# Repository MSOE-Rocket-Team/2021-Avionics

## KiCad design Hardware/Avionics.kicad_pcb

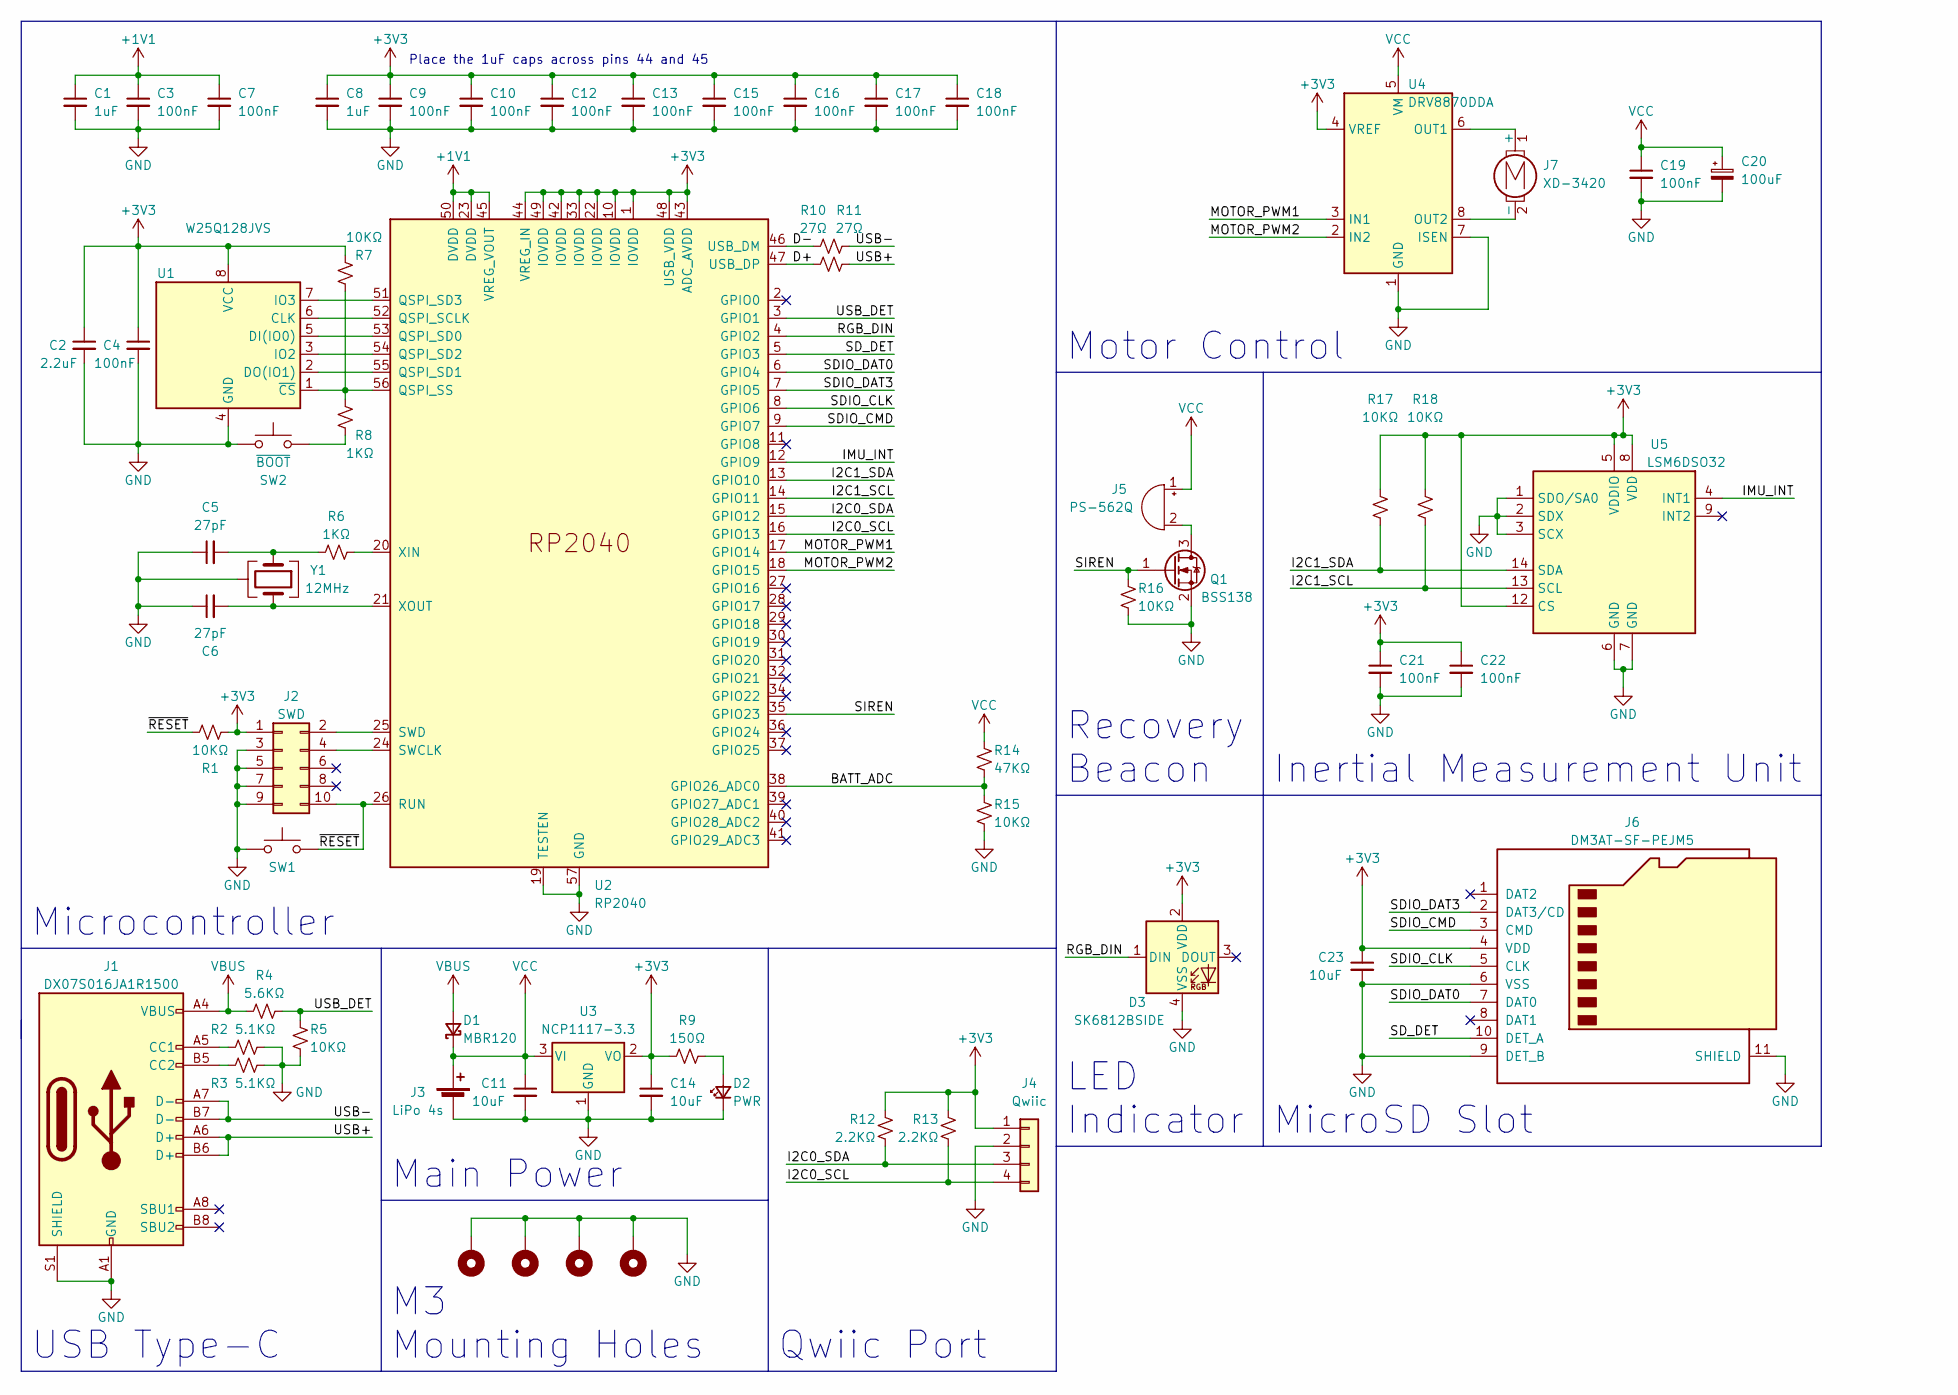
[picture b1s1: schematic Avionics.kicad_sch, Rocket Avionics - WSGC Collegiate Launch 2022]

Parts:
C1, C8: 1uF; C_0402_1005Metric
C2: 2.2uF; C_0603_1608Metric
C3, C4, C7, C9, C10, C12, C13, C15, C16, C17, C18, C19, C21, C22: 100nF; C_0402_1005Metric
C5, C6: 27pF; C_0603_1608Metric
C11, C14, C23: 10uF; C_0805_2012Metric
C20: 100uF; CP_Elec_8x6.5
D1: MBR120; D_SOD-123F
D2: PWR; LED_0603_1608Metric
D3: SK6812BSIDE; SK6812B_Side
H1, H2, H3, H4: M3; MountingHole_3.2mm_M3_Pad
J1: DX07S016JA1R1500
J2: SWD; PinHeader_2x05_P1.27mm_Vertical_SMD
J3: LiPo 4s; AMASS_XT60PW-M
J4: Qwiic; JST_SH_BM04B-SRSS-TB_1x04-1MP_P1.00mm_Vertical
J5: PS-562Q; JST_XH_B2B-XH-A_1x02_P2.50mm_Vertical
J6: DM3AT-SF-PEJM5; microSD_HC_Hirose_DM3AT-SF-PEJM5
J7: XD-3420; TerminalBlock_Phoenix_PT-1,5-2-3.5-H_1x02_P3.50mm_Horizontal
Q1: BSS138; SOT-23
R1, R5, R7, R15, R16, R17, R18: 10KΩ; R_0603_1608Metric
R2, R3: 5.1KΩ; R_0603_1608Metric
R4: 5.6KΩ; R_0603_1608Metric
R6, R8: 1KΩ; R_0603_1608Metric
R9: 150Ω; R_0603_1608Metric
R10, R11: 27Ω; R_0402_1005Metric
R12, R13: 2.2KΩ; R_0603_1608Metric
R14: 47KΩ; R_0603_1608Metric
SW1: ~{RESET}; SW_SPST_B3U-1000P
SW2: ~{BOOT}; SW_SPST_B3U-1000P
U1: W25Q128JVS; SOIC-8_5.23x5.23mm_P1.27mm
U2: RP2040; RP2040-QFN-56
U3: NCP1117-3.3; SOT-223-3_TabPin2
U4: DRV8870DDA; Texas_HTSOP-8-1EP_3.9x4.9mm_P1.27mm_EP2.95x4.9mm_Mask2.4x3.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
U5: LSM6DSO32; LGA-14_3x2.5mm_P0.5mm_LayoutBorder3x4y
Y1: 12MHz; Crystal_SMD_Abracon_ABM8G-4Pin_3.2x2.5mm

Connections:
+1V1: C1.1, C3.1, C7.1, U2.23 (DVDD), U2.45 (VREG_VOUT), U2.50 (DVDD)
+3V3: C2.1, C4.1, C8.1, C9.1, C10.1, C12.1, C13.1, C14.1, C15.1, C16.1, C17.1, C18.1, C21.1, C22.1, C23.1, D3.2 (VDD), J2.1, J4.1, J6.4 (VDD), R1.2, R7.1, R9.1, R12.1, R13.1, R17.1, R18.1, U1.8 (VCC), U2.1 (IOVDD), U2.10 (IOVDD), U2.22 (IOVDD), U2.33 (IOVDD), U2.42 (IOVDD), U2.43 (ADC_AVDD), U2.44 (VREG_IN), U2.48 (USB_VDD), U2.49 (IOVDD), U3.2 (VO), U4.4 (VREF), U5.5 (VDDIO), U5.8 (VDD), U5.12 (CS)
/BATT_ADC: R14.2, R15.1, U2.38 (GPIO26_ADC0)
/D+: R11.1, U2.47 (USB_DP)
/D-: R10.1, U2.46 (USB_DM)
/I2C0_SCL: J4.4, R13.2, U2.16 (GPIO13)
/I2C0_SDA: J4.3, R12.2, U2.15 (GPIO12)
/I2C1_SCL: R18.2, U2.14 (GPIO11), U5.13 (SCL)
/I2C1_SDA: R17.2, U2.13 (GPIO10), U5.14 (SDA)
/IMU_INT: U2.12 (GPIO9), U5.4 (INT1)
/MOTOR_PWM1: U2.17 (GPIO14), U4.3 (IN1)
/MOTOR_PWM2: U2.18 (GPIO15), U4.2 (IN2)
/RGB_DIN: D3.1 (DIN), U2.4 (GPIO2)
/SDIO_CLK: J6.5 (CLK), U2.8 (GPIO6)
/SDIO_CMD: J6.3 (CMD), U2.9 (GPIO7)
/SDIO_DAT0: J6.7 (DAT0), U2.6 (GPIO4)
/SDIO_DAT3: J6.2 (DAT3/CD), U2.7 (GPIO5)
/SD_DET: J6.10 (DET_A), U2.5 (GPIO3)
/SIREN: Q1.1 (G), R16.1, U2.35 (GPIO23)
/USB+: J1.A6 (D+), J1.B6 (D+), R11.2
/USB-: J1.A7 (D-), J1.B7 (D-), R10.2
/USB_DET: R4.2, R5.1, U2.3 (GPIO1)
/~RESET: J2.10, R1.1, SW1.2, U2.26 (RUN)
GND: C1.2, C2.2, C3.2, C4.2, C5.1, C6.1, C7.2, C8.2, C9.2, C10.2, C11.2, C12.2, C13.2, C14.2, C15.2, C16.2, C17.2, C18.2, C19.2, C20.2, C21.2, C22.2, C23.2, D2.1 (K), D3.4 (VSS), H1.1, H2.1, H3.1, H4.1, J1.A1 (GND), J1.A12 (GND), J1.B1 (GND), J1.B12 (GND), J1.S1 (SHIELD), J2.3, J2.5, J2.7, J2.9, J3.2 (-), J4.2, J6.6 (VSS), J6.9 (DET_B), J6.11 (SHIELD), Q1.2 (S), R2.2, R3.2, R5.2, R15.2, R16.2, SW1.1, SW2.1, U1.4 (GND), U2.19 (TESTEN), U2.57 (GND), U3.1 (GND), U4.1 (GND), U4.7 (ISEN), U4.9 (GND), U5.1 (SDO/SA0), U5.2 (SDX), U5.3 (SCX), U5.6 (GND), U5.7 (GND), Y1.2, Y1.4
unnamed: C5.2, R6.1, Y1.1
unnamed: C6.2, U2.21 (XOUT), Y1.3
unnamed: D2.2 (A), R9.2
unnamed: J1.A5 (CC1), R2.1
unnamed: J1.B5 (CC2), R3.1
unnamed: J2.2, U2.25 (SWD)
unnamed: J2.4, U2.24 (SWCLK)
unnamed: J5.2 (+), Q1.3 (D)
unnamed: J7.1 (+), U4.6 (OUT1)
unnamed: J7.2 (-), U4.8 (OUT2)
unnamed: R6.2, U2.20 (XIN)
unnamed: R7.2, R8.1, U1.1 (~CS), U2.56 (QSPI_SS)
unnamed: R8.2, SW2.2
unnamed: U1.2 (DO(IO1)), U2.55 (QSPI_SD1)
unnamed: U1.3 (IO2), U2.54 (QSPI_SD2)
unnamed: U1.5 (DI(IO0)), U2.53 (QSPI_SD0)
unnamed: U1.6 (CLK), U2.52 (QSPI_SCLK)
unnamed: U1.7 (IO3), U2.51 (QSPI_SD3)
VBUS: D1.2 (A), J1.A4 (VBUS), J1.A9 (VBUS), J1.B4 (VBUS), J1.B9 (VBUS), R4.1
VCC: C11.1, C19.1, C20.1, D1.1 (K), J3.1 (+), J5.1 (-), R14.1, U3.3 (VI), U4.5 (VM)

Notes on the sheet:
Place the 1uF caps across pins 44 and 45
Recovery Beacon
LED Indicator
Microcontroller
M3 Mounting Holes
Inertial Measurement Unit
MicroSD Slot
Main Power
USB Type-C
Qwiic Port
Motor Control

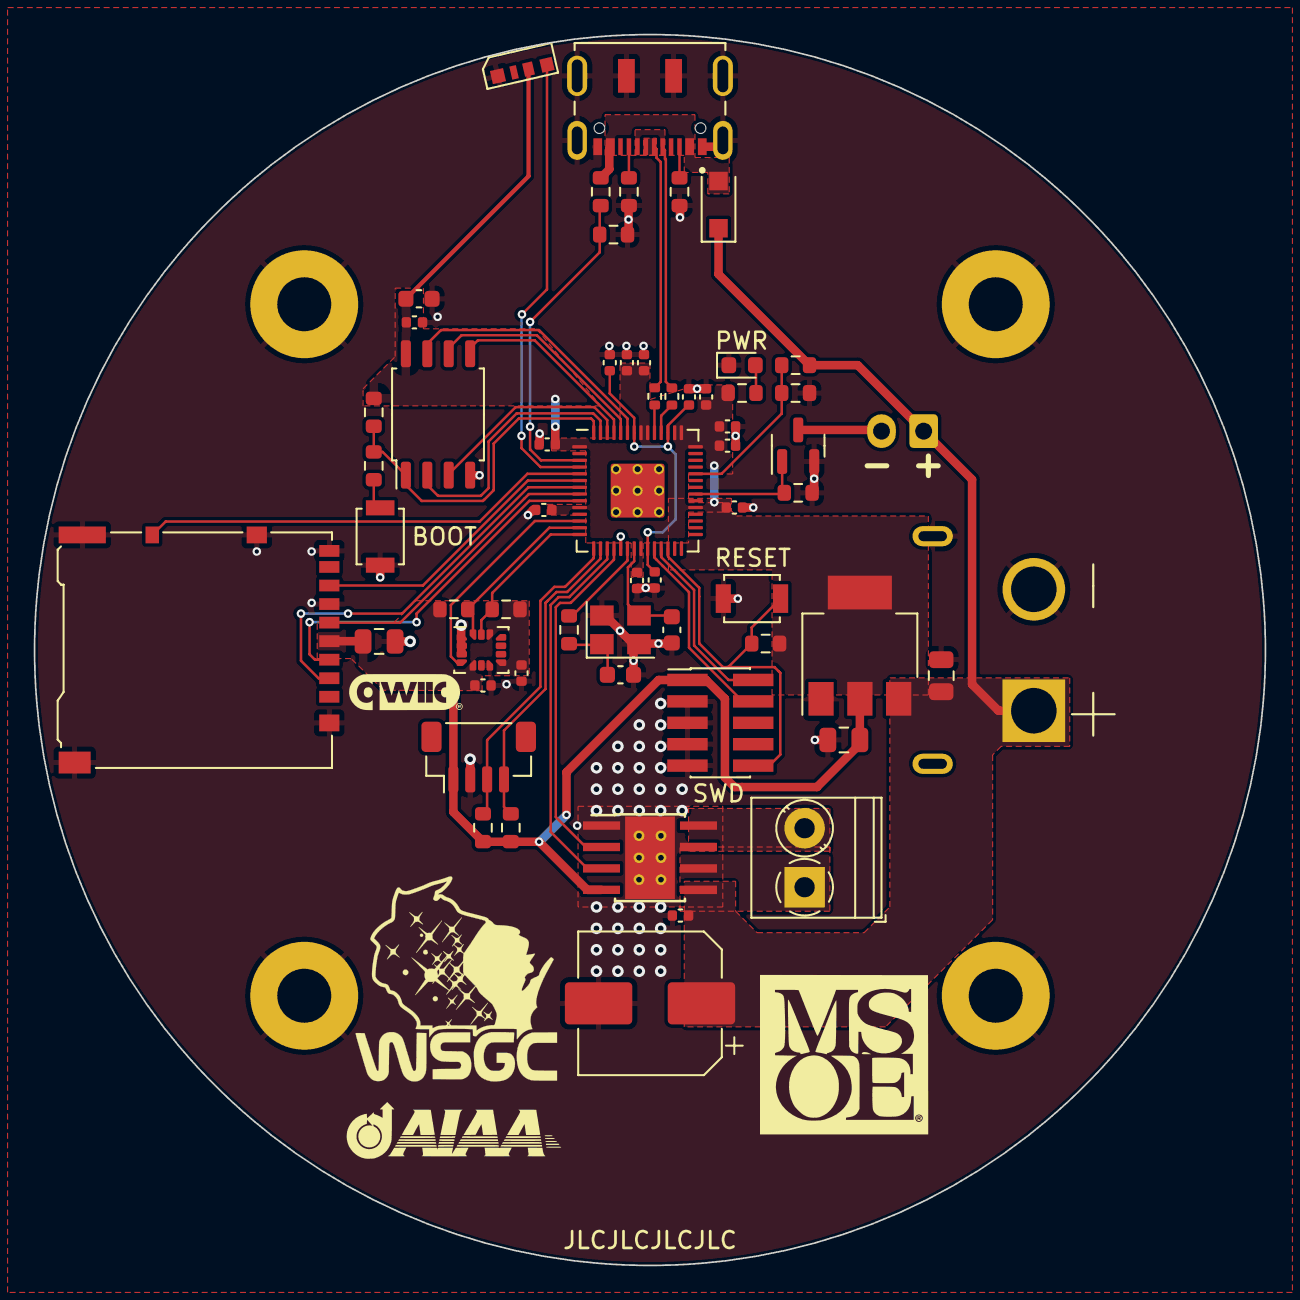
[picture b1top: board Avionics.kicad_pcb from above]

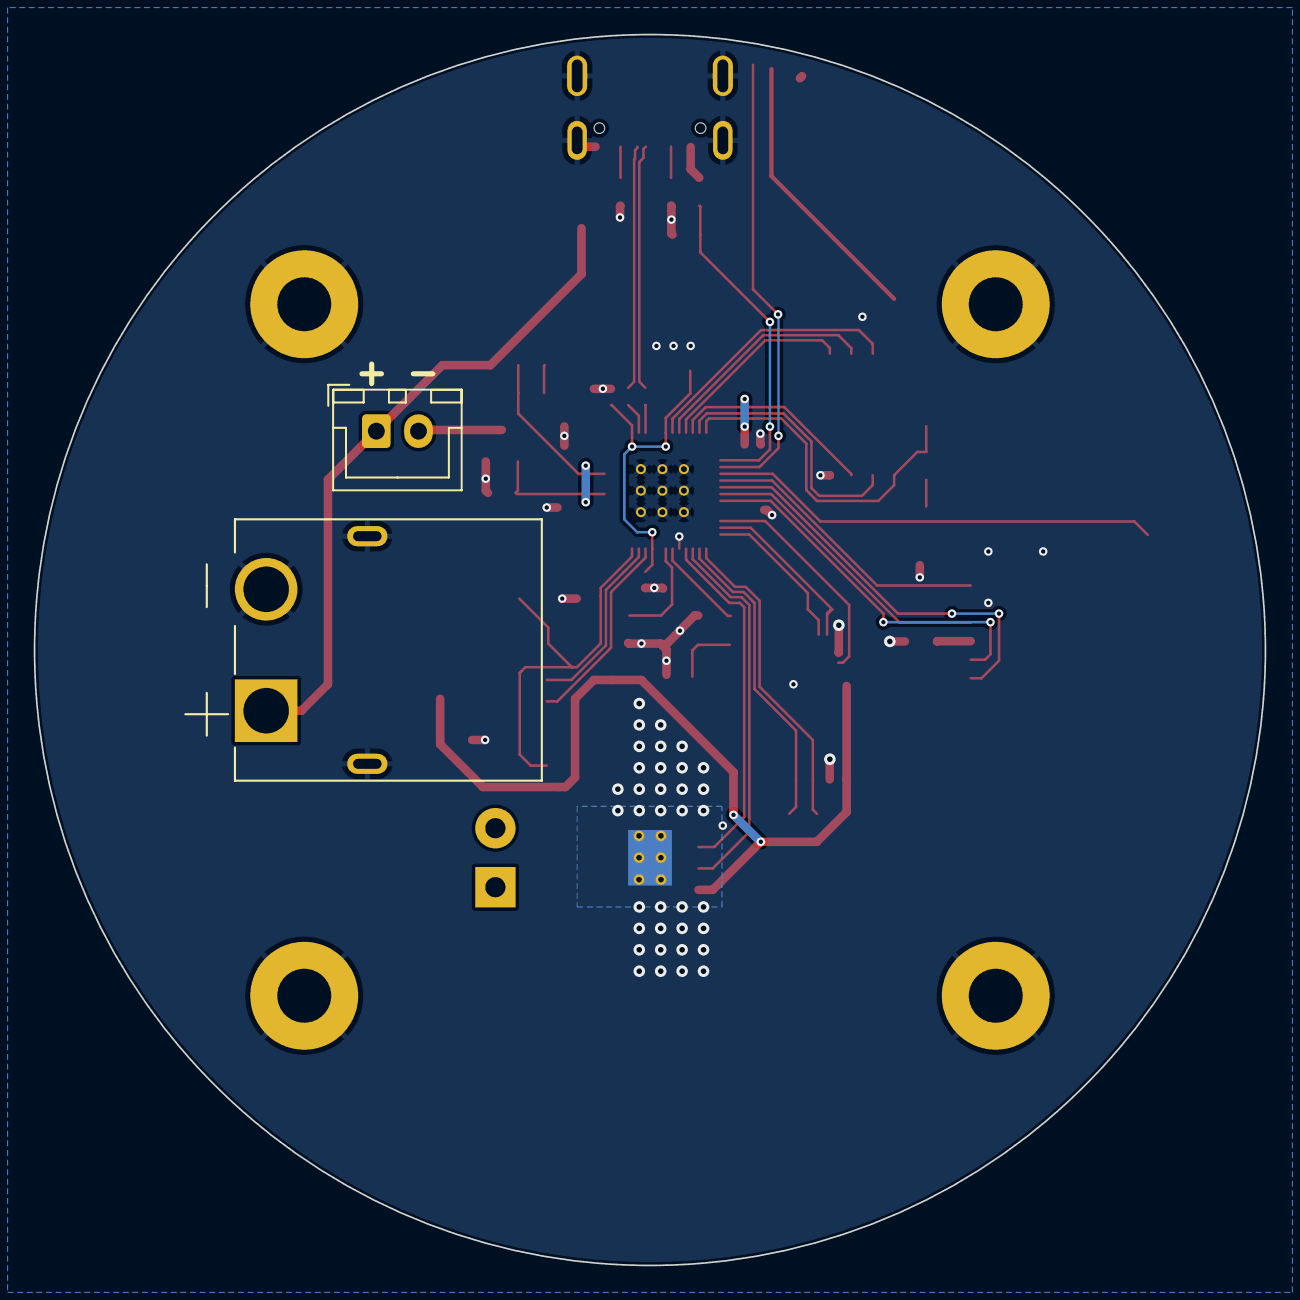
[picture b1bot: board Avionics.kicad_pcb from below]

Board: 2 copper layers, 73.0 x 73.0 mm, 64 parts (2 on the bottom side), 44 nets.

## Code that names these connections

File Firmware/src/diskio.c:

#include "pico/stdlib.h"
#include "pico/printf.h"
#include "hardware/spi.h"

#include "crc.h"
#include "diskio.h"

#define SD_DET    3   // Card detect
#define SDIO_DAT0 4   // Data Out
#define SDIO_DAT3 5   // Chip select
#define SDIO_CLK  6   // Clock
#define SDIO_CMD  7   // Data In

#define CMD0    (0x40 + 0)  // GO_IDLE_STATE:     Software reset
#define CMD1    (0x40 + 1)  // SEND_OP_COND:      Send host capacity info and activate init process
#define CMD8    (0x40 + 8)  // SEND_IF_COND:      Send host voltage info and gets operational range
#define CMD16   (0x40 + 16) // SET_BLOCKLEN:      Set card block length; fixed to 512 for SDHC & XC
#define CMD17   (0x40 + 17) // READ_SINGLE_BLOCK: Read block of size selected by SET_BLOCKLEN
#define CMD24   (0x40 + 24) // WRITE_BLOCK:       Write block of size selected by SET_BLOCKLEN
#define CMD55   (0x40 + 55) // APP_CMD:           Next command is application specific
#define CMD58   (0x40 + 58) // READ_OCR:          Read OCR register of card
#define ACMD41  (0xC0 + 41) // SD_SEND_OP_COND:   Send host capacity info and activate init process

enum CARD_TYPE {
  UNKNOWN,    // Unknown device
  MMCV3,      // MMC version 3
  SDV1,       // SD version 1
  SDV2_BYTE,  // SD version 2 byte addressing
  SDV2_BLOCK, // SD version 2 block addressing
};

static enum CARD_TYPE card_type = UNKNOWN;

// Chip select active low
static inline void chip_select(uint gpio) {
  asm volatile("nop \n nop \n nop");
  gpio_put(gpio, 0);
  asm volatile("nop \n nop \n nop");
}

// Chip deselect active low
static inline void chip_deselect(uint gpio) {
  asm volatile("nop \n nop \n nop");
  gpio_put(gpio, 1);
  asm volatile("nop \n nop \n nop");
}

// Send SPI command
void send_cmd(BYTE cmd, DWORD arg, uint8_t* dst, size_t len) {
  if (cmd & 0x80) { // Handle ACMD# command sequence
    cmd &= 0x7F;  // Command variable falls thru
    uint8_t data[] = {0};
    send_cmd(CMD55, 0, data, 1);  // Prelude by CMD55
    if (data[0]) {  // Error on CMD55; return immediate
      if (len != 0) dst[0] = data[0];
      return;
    }
  }

  uint8_t buf[] = {
      cmd,
      (BYTE)(arg >> 24),
      (BYTE)(arg >> 16),
      (BYTE)(arg >> 8),
      (BYTE)arg,
      0
  };
  buf[5] = (crc7(buf, 5) << 1) + 1; // Calculate CRC and end bit

  printf("send_cmd: send");
  for (int i = 0; i < 6; i++) {
    printf(" %x", buf[i]);
  }
  printf("\n");

  chip_select(SDIO_DAT3);
  spi_write_blocking(spi0, (uint8_t[]){0xFF}, 1); // Dummy byte
  spi_write_blocking(spi0, buf, 6);
  if (len != 0) spi_read_blocking(spi0, 0x00, dst, len);
  chip_deselect(SDIO_DAT3);

  printf("send_cmd: recv");
  while (len--) {
    printf(" %x", dst[len]);
  }
  printf("\n");
}

// Initialize Disk Drive
DSTATUS disk_initialize() {
  DSTATUS stat = STA_NOINIT;

  // Initialize SPI clock and data pins
  spi_init(spi0,200000); // 200kHz baudrate
  gpio_set_function(SDIO_DAT0, GPIO_FUNC_SPI);
  gpio_set_function(SDIO_CLK, GPIO_FUNC_SPI);
  gpio_set_function(SDIO_CMD, GPIO_FUNC_SPI);

  // Chip select active low
  gpio_init(SDIO_DAT3);
  gpio_set_dir(SDIO_DAT3, GPIO_OUT);
  chip_deselect(SDIO_DAT3);

  // Detect if SD card inserted
  gpio_init(SD_DET);
  gpio_set_dir(SD_DET, GPIO_IN);
  if (gpio_get(SD_DET)) {
    return STA_NODISK;
  }

  // 80 dummy clock cycles
  sleep_ms(1);
  spi_write_blocking(spi0, (uint8_t[]){
    0xFF, 0xFF, 0xFF, 0xFF, 0xFF,
    0xFF, 0xFF, 0xFF, 0xFF, 0xFF
    }, 10);

  uint8_t data[] = {0, 0, 0, 0, 0};
  int n = 10;
  do {
    sleep_ms(100);
    send_cmd(CMD0, 0, data, 1); // Software reset
  } while (--n && data[0] != 0x01);
  if (data[0] == 0x01) {
    send_cmd(CMD8, 0x1AA, data, 5);
    if (data[0] == 0x01) {  // SDv2
      if (data[3] == 0x01 && data[4] == 0xAA) { // Works at VDD range of 2.7-3.6V
        uint tmr = 10000;
        do {  // Wait for leaving idle state (ACMD41 with High Capacity Support)
          sleep_us(100);
          send_cmd(ACMD41, 1 << 30, data, 1);
        } while (--tmr && data[0]);

        send_cmd(CMD58, 0, data, 5);
        if (tmr && data[0] == 0) {  // Check CCS bit in the OCR
          card_type = (data[1] & 0x40) ? SDV2_BLOCK : SDV2_BYTE;	// SD version 2 block/byte addr.
          if (card_type == SDV2_BYTE) {
            send_cmd(CMD16, 512, data, 1);  // Force block size to 512 bytes
            if (data[0] == 0) {
              stat = 0x00;  // Successfully initialized
            }
          } else {
            stat = 0x00;  // Successfully initialized
          }
        }
      }
    } else {  // SDv1 or MMCv3
      uint tmr = 10000;
      send_cmd(ACMD41, 0, data, 1);
      if (data[0] <= 1) {
        card_type = SDV1; // SD version 1
        do {  // Wait for leaving idle state
          sleep_us(100);
          send_cmd(ACMD41, 0, data, 1);
        } while (--tmr && data[0]);
      } else {
        card_type = MMCV3;  // MMC version 3
        do {  // Wait for leaving idle state
          sleep_us(100);
          send_cmd(CMD1, 0, data, 1);
        } while (--tmr && data[0]);
      }

      send_cmd(CMD16, 512, data, 1);  // Force block size to 512 bytes
      if (tmr && data[0] == 0) {
        stat = 0x00;  // Successfully initialized
      }
    }
  }

  printf("card status: %d\ncard type: %d\n", stat, card_type);
  return stat;
}

// Read Partial Sector
DRESULT disk_readp(BYTE* buff, DWORD sector, UINT offset, UINT count) {
  DRESULT res = RES_ERROR;

  if (card_type == SDV2_BLOCK) sector *= 512; // Convert to byte address if needed

  uint8_t data[] = {0};
  send_cmd(CMD17, sector, data, 1); // Read data block
  if (data[0] == 0) {
    chip_select(SDIO_DAT3); // Ready chip for consecutive read

    uint tmr = 40000;
    do {  // Wait for data token
      spi_read_blocking(spi0, 0xFF, data, 1);
    } while (--tmr && data[0] == 0xFF);

    if (tmr && data[0] == 0xFE) {  // Data token arrived
      // Skip leading bytes from offset
      while (offset--) spi_read_blocking(spi0, 0xFF, data, 1);

      // Receive part of the sector
      spi_read_blocking(spi0, 0xFF, buff, count);

      // Skip trailing bytes and CRC
      uint trailing = 512 + 2 - offset - count; // Number of trailing bytes to skip
      uint8_t discard[trailing];
      spi_read_blocking(spi0, 0xFF, discard, trailing);

      res = RES_OK;
    }
  }

  chip_deselect(SDIO_DAT3);
  return res;
}

// Write Partial Sector
DRESULT disk_writep(const BYTE* buff, DWORD sc) {
  DRESULT res = RES_ERROR;
  static uint wc; // Sector write counter

  if (!buff) {
    if (sc) { // Initiate a sector write transaction
      if (card_type == SDV2_BLOCK) sc *= 512; // Convert to byte address if needed

      uint8_t data[] = {0};
      send_cmd(CMD24, sc, data, 1);
      if (data[0] == 0) {
        chip_select(SDIO_DAT3);  // Ready chip for consecutive write

        spi_write_blocking(spi0, (uint8_t[]){0xFF, 0xFE}, 2); // write padding + data block header
        wc = 512; // Set write counter
        res = RES_OK;
      }
    } else {  // Finalize a sector write transaction
      wc += 2;  // Fill remaining bytes and CRC with zeroes
      while (wc--) spi_write_blocking(spi0, (uint8_t[]){0x00}, 1);
      uint8_t data[] = {0};
      spi_read_blocking(spi0, 0xFF, data, 1);
      if ((data[0] & 0x1F) == 0x05) { // Data response token status "accepted"
        uint tmr = 5000;
        do {  // Block while card busy
          sleep_us(100);
          spi_read_blocking(spi0, 0xFF, data, 1);
        } while (--tmr && data[0] != 0xFF);
        if (tmr) res = RES_OK;
      }

      chip_deselect(SDIO_DAT3); // Release chip from consecutive write
    }
  } else {  // Perform sector write transaction
    while (wc-- && sc--) {
      spi_write_blocking(spi0, buff++, 1);  // Write each byte in buff while wc >= 0
    }
    res = RES_OK;
  }

  return res;
}

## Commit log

2021-11-29 Created directory structure and initial KiCAD project
2021-11-29 Fixed directories and added initial Arduino sketch
2021-11-29 Fixed Arduino project
2021-12-30 Updated project files to KiCAD 6.0 release
2022-01-08 Added most parts to schematic and created library part for RP2040
2022-01-08 Add L298P driver
2022-02-24 Layout complete, pending review
2022-02-24 Fixed part libraries
2022-03-15 Modified layout
2022-03-16 Moved reference designators to fab layer
2022-03-18 Added silkscreen logos and improved power routing
2022-03-25 Initialize firmware
2022-03-25 Add PID
2022-03-27 Rename pid and enable serial
2022-03-28 Add motor control
2022-03-30 Add IMU
2022-04-07 Final layout
2022-04-07 Added images
2022-04-09 Add sd card lib
2022-04-15 Add pff and write disk init
2022-04-20 Finalize untested SD read/write
2022-04-21 Add dummy clock cycles
2022-04-26 Try to fix sd card
